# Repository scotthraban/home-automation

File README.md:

A collection of different parts of the home automation solution that I have built up over time for my house. The longer that things have been running, the less that I remember how they work, and where to find all the bits that go into each part of the whole.

So this is really more for me than for anyone else, but if anything I put up here ends up being helpful to anyone else, that would be awesome.

# Sensors
 - [ESP8266 Temperature Sensor](sensors/esp-temperature-sensor)
 - [Arduino Temperature Sensor (deprecated)](sensors/arduino-temperature-sensor)
 - [Arduino Temperature Humidity Sensor (deprecated)](sensors/arduino-temperature-humidity-sensor)
 - [ESP8266 AQI and Temperature Sensor](sensors/esp-air-quality-sensor)

# Controllers
 - [Arduino MySensors Furnance Controller (deprecated)](controllers/arduino-furnace-controller)

# Gateway
 - [Arduino MySensors Serial Gateway (deprecated)](openhab/arduino-serial-gateway)

# External Data Sources
 - [PurpleAir to openHAB over MQTT](purple-air)
 
# Notification / Alerting
 - [Telegram Bot](telegram-bot)

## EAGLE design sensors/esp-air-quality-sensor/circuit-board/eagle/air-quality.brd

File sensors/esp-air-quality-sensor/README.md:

# Air Quality Sensor

This project runs on an ESP8266, using MQTT over Wifi to send the air quality and temperature information back to openHAB.

## Software

[Arduino project for ESP8266 board](esp8266-mqtt-panasonic-air-quality-sensor).

## Wiring Schematic

## Circuit Board

[Eagle project](circuit-board/eagle)

I used the [OSH Park](https://oshpark.com/) service to fabricate the board for this project, sending them [just the board file](circuit-board/eagle/air-quality.brd).

## Project Box

Designed in Autodesk Fusion 360, available on [Thingiverse](https://www.thingiverse.com/thing:4777796).

## BOM

 - ESP-01S Wifi microcontroller ([something like this](https://www.amazon.com/gp/product/B01N98BTRH/ref=ppx_od_dt_b_asin_title_s00?ie=UTF8&psc=1))
 - [Panasonic SN-GCJA5](https://www.sparkfun.com/products/17123)
 - DS18B20 temperature sensor ([TO92](https://www.digikey.com/product-detail/en/maxim-integrated/DS18B20-/DS18B20--ND/956983)
 - AMS1117 3pin stepdown breakout board ([one of many to be found](https://www.amazon.com/gp/product/B07CP4P5XJ/ref=ppx_yo_dt_b_asin_title_o03_s00?ie=UTF8&psc=1))
 - 2x 4.7k Ohm resistors ([no particular reason to use these](https://www.amazon.com/gp/product/B0185FIIVE/ref=ppx_yo_dt_b_asin_title_o01_s00?ie=UTF8&psc=1))
 - 2.54mm Pitch 2X4 8 Pin Female Double Row Straight Header PCB Connector ([I used these](https://www.amazon.com/gp/product/B01IHBCO2K/ref=ppx_yo_dt_b_asin_title_o09_s00?ie=UTF8&psc=1))
 - USB Micro B power connector ([parallel](https://www.digikey.com/product-detail/en/amphenol-icc-fci/10118194-0001LF/609-4618-1-ND/2785382) or [perpendicular](https://www.digikey.com/product-detail/en/gct/USB3131-30-0230-A/2073-USB3131-30-0230-ACT-ND/9859713) to the board) 
 - 5v USB power supply (I just used one of the many that I have from dead cell phones and such)

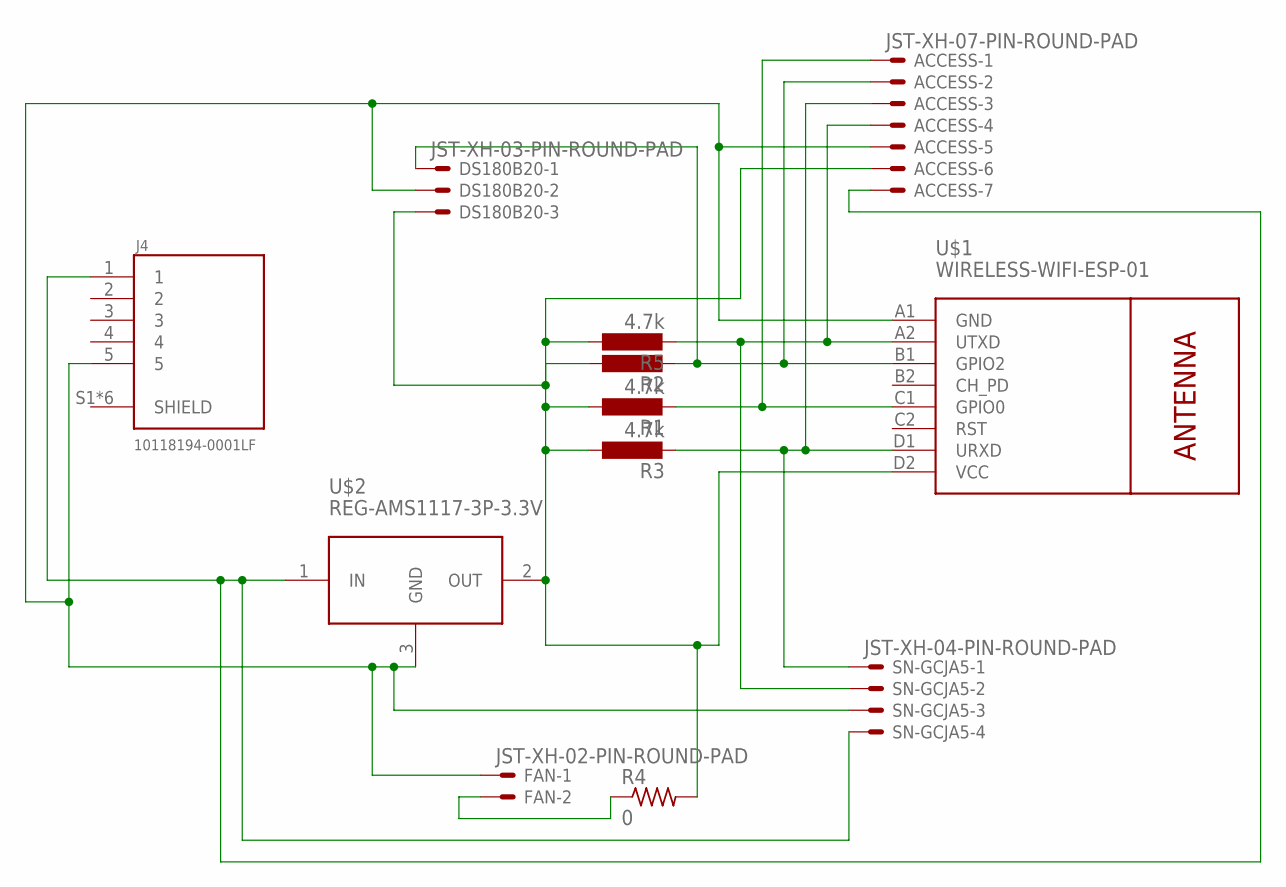
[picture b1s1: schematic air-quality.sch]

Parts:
ACCESS: JST-XH-07-PIN-ROUND-PAD; JST-XH-07-PACKAGE-ROUND-PAD
DS180B20: JST-XH-03-PIN-ROUND-PAD; JST-XH-03-PACKAGE-ROUND-PAD
FAN: JST-XH-02-PIN-ROUND-PAD; JST-XH-02-PACKAGE-ROUND-PAD
J4: 10118194-0001LF; AMPHENOL_10118194-0001LF
R1, R2, R3, R5: 4.7k; 0207/10
R4: 0; 0204V
SN-GCJA5: JST-XH-04-PIN-ROUND-PAD; JST-XH-04-PACKAGE-ROUND-PAD
U$1: WIRELESS-WIFI-ESP-01
U$2: REG-AMS1117-3P-3.3V; REG-AMS1117-3P

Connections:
3.3V: ACCESS.6, DS180B20.3, R1.1, R2.1, R3.1, R4.2, R5.1, U$1.D2 (VCC), U$2.2 (OUT)
5V: ACCESS.7, J4.1, SN-GCJA5.4, U$2.1 (IN)
GND: ACCESS.5, DS180B20.2, FAN.1, J4.5, SN-GCJA5.3, U$1.A1 (GND), U$2.3 (GND)
GPIO0: ACCESS.1, R1.2, U$1.C1 (GPIO0)
GPIO2: ACCESS.2, DS180B20.1, R2.2, U$1.B1 (GPIO2)
unnamed: FAN.2, R4.1
RX: ACCESS.3, R3.2, SN-GCJA5.1, U$1.D1 (URXD)
TX: ACCESS.4, R5.2, SN-GCJA5.2, U$1.A2 (UTXD)

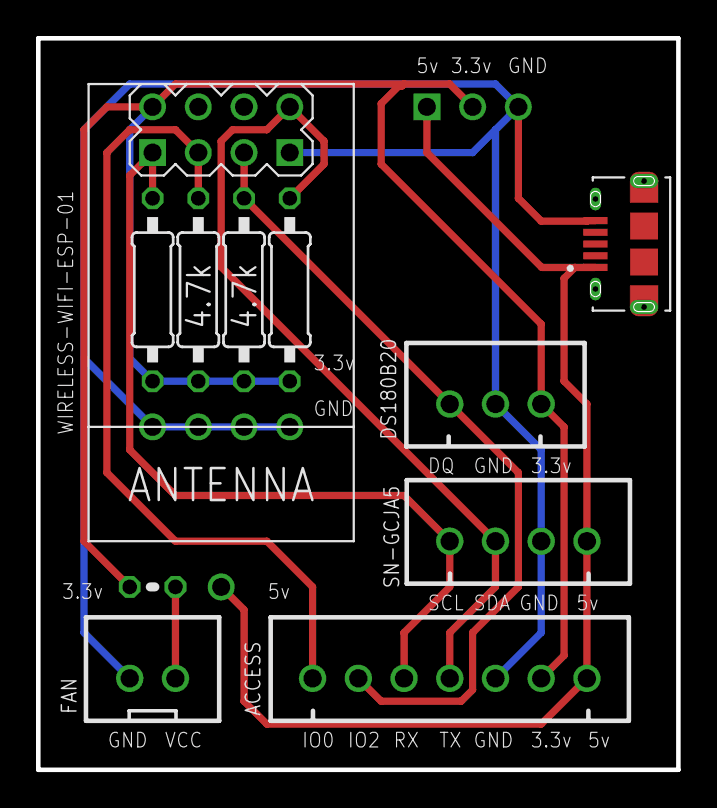
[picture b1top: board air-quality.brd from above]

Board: 2 copper layers, 35.6 x 40.6 mm, 12 parts (1 on the bottom side), 8 nets.

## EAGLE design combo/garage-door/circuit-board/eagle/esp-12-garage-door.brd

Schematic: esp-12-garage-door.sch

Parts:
2N2222: 2N2222-NPN-TO92-EBC; TO92-EBC
NODEMCU: NODEMCU
R2: 33; 0207/7
R3: 10k; 0207/7
R5: 470; 0207/7
R6: 1k; 0207/7
REED: REED_SWITCH-PTH-INSULATED; REED_SWITCH_PLASTIC
RELAY: JSM1-12V-5

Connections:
3V: NODEMCU.11 (3V), NODEMCU.25 (3V)
GND: 2N2222.E, NODEMCU.2 (GND), NODEMCU.10 (GND), NODEMCU.14 (GND), NODEMCU.17 (GND), NODEMCU.24 (GND), R3.2
unnamed: NODEMCU.15 (VIN), R2.2
unnamed: 2N2222.C, RELAY.5
unnamed: NODEMCU.28 (D2), R3.1, REED.P$2 (2)
unnamed: R2.1, RELAY.2
unnamed: 2N2222.B, R5.2
unnamed: NODEMCU.16 (3V), R6.1
unnamed: NODEMCU.29 (D1), R5.1
unnamed: R6.2, REED.P$1 (1)

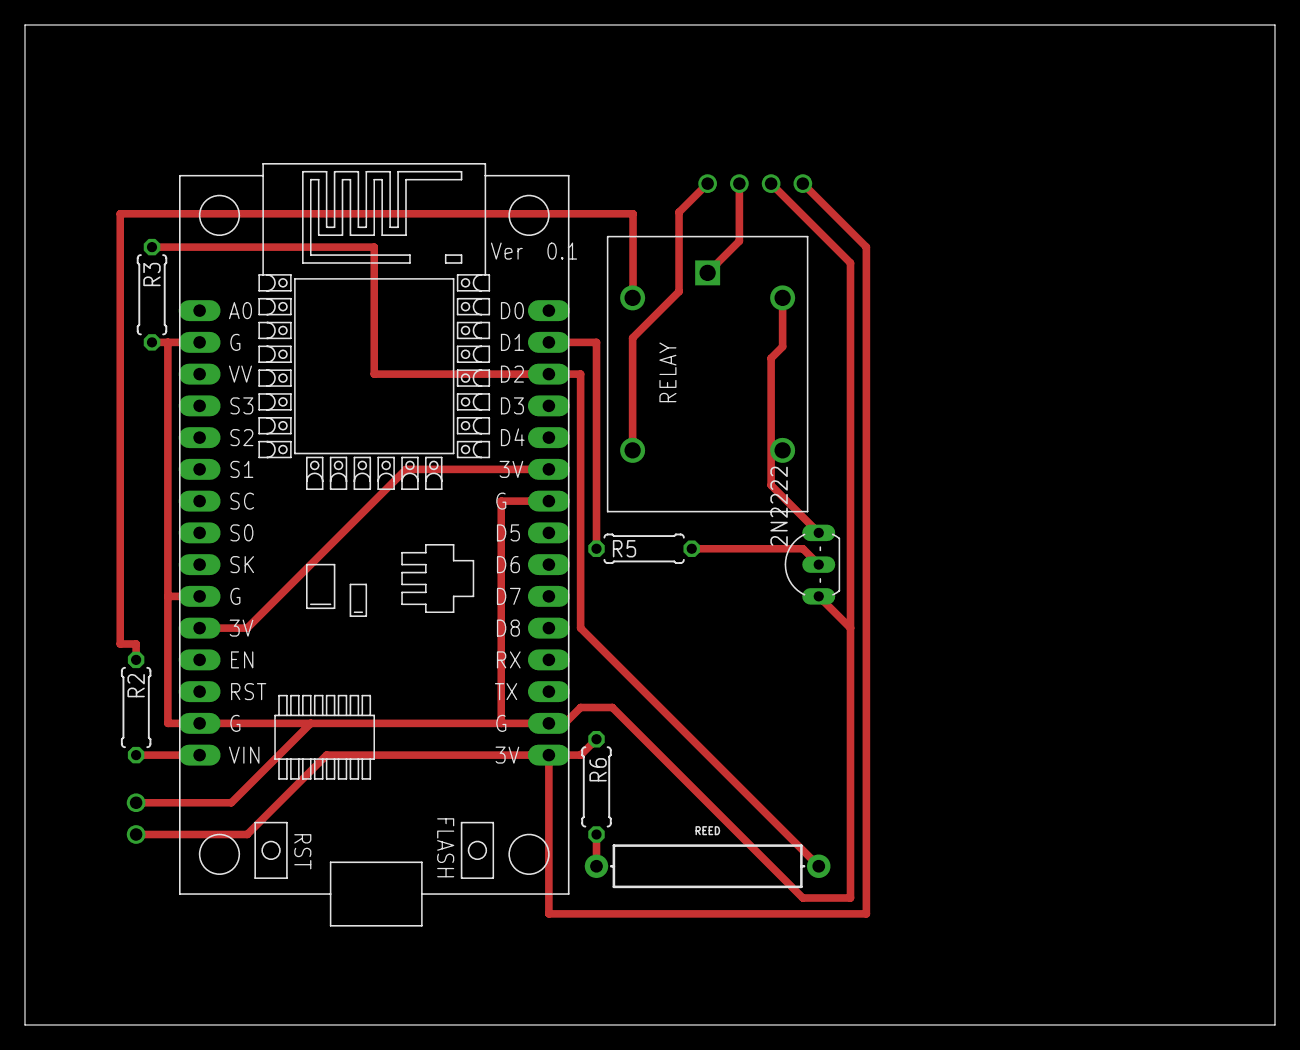
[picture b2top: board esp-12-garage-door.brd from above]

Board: 2 copper layers, 100.0 x 80.0 mm, 8 parts (0 on the bottom side), 10 nets.

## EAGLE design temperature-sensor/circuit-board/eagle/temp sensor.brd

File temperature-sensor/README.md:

# Temperature Sensor

This project runs on an ESP8266, using MQTT over Wifi to send the temperature back to openHAB.

I created a custom circuit board to make it a little more durable and reliable.

I have used both the TO92 and the waterproof probes.

I ran into a fair bit of issues with heat from the components being picked up by the sensor, even with the extended traces on the circuit board. In the end I gave on on elegant solutions and just stuck a fan on the thing to keep the ambient air circulating over the sensor. The fan is only being driven by 5v, but I used a 12v fan so that it would spin slow, and thus be quiet, to assist in the WAF of the project. Unfortunately that also meant that the fan sometimes does not have enough voltage to start spinning - once it is going it is fine, but it sometimes needs a push.

## Software

[Arduino project for ESP8266 board](esp8266-mqtt-single-ds18b20-sensor).

## Wiring Schematic

## Circuit Board

[Eagle project](circuit-board)

I used the [OSH Park](https://oshpark.com/) service to fabricate the board for this project, sending them [this zip file](circuit-board/export/temp sensor_2020-01-11.zip) with the Gerber (and other) files.

## Project Box

Designed in Autodesk Fusion 360, available on [Thingiverse](https://www.thingiverse.com/thing:4508169).

## BOM

 - ESP-01S Wifi microcontroller ([something like this](https://www.amazon.com/gp/product/B01N98BTRH/ref=ppx_od_dt_b_asin_title_s00?ie=UTF8&psc=1))
 - DS18B20 temperature sensor ([TO92](https://www.digikey.com/product-detail/en/maxim-integrated/DS18B20-/DS18B20--ND/956983) or [waterproof](https://www.amazon.com/Gikfun-DS18B20-Temperature-Waterproof-EK1083x3/dp/B012C597T0/ref=sr_1_3?crid=3AA1NY9ENGP12&dchild=1&keywords=ds18b20&qid=1593380354&sprefix=ds18%2Caps%2C232&sr=8-3))
 - AMS1117 3pin stepdown breakout board ([one of many to be found](https://www.amazon.com/gp/product/B07CP4P5XJ/ref=ppx_yo_dt_b_asin_title_o03_s00?ie=UTF8&psc=1))
 - 2x 4.7k Ohm resistors ([no particular reason to use these](https://www.amazon.com/gp/product/B0185FIIVE/ref=ppx_yo_dt_b_asin_title_o01_s00?ie=UTF8&psc=1))
 - 2.54mm Pitch 2X4 8 Pin Female Double Row Straight Header PCB Connector ([I used these](https://www.amazon.com/gp/product/B01IHBCO2K/ref=ppx_yo_dt_b_asin_title_o09_s00?ie=UTF8&psc=1))
 - 30x30x10mm 2pin 12v computer fan ([not great but it worked](https://www.amazon.com/gp/product/B071KK1KBG/ref=ppx_yo_dt_b_asin_title_o09_s00?ie=UTF8&psc=1))
 - USB Micro B power connector ([parallel](https://www.digikey.com/product-detail/en/amphenol-icc-fci/10118194-0001LF/609-4618-1-ND/2785382) or [perpendicular](https://www.digikey.com/product-detail/en/gct/USB3131-30-0230-A/2073-USB3131-30-0230-ACT-ND/9859713) to the board) 
 - 5v USB power supply (I just used one of the many that I have from dead cell phones and such)

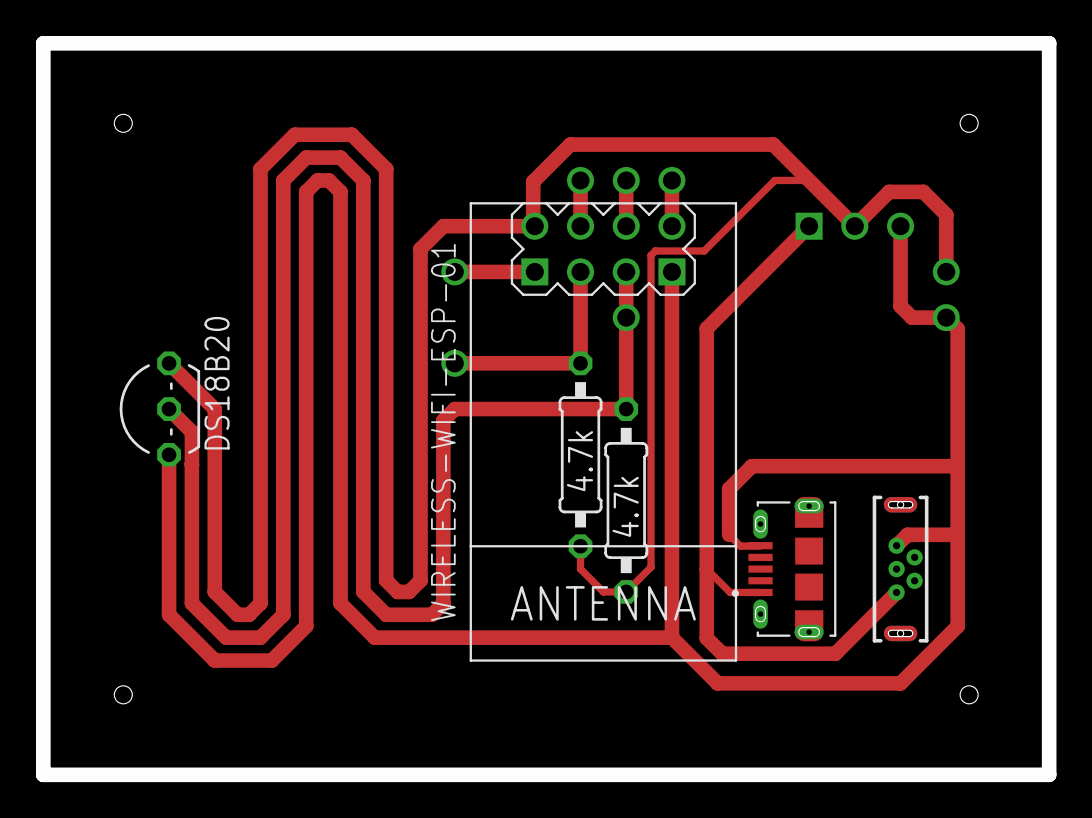
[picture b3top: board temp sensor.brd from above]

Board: 2 copper layers, 55.9 x 40.6 mm, 7 parts (1 on the bottom side), 5 nets.

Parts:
IC1: DS18B20; TO92-
J1: USB3131-XX-0230-X_REVB; GCT_USB3131-XX-0230-X_REVB
J4: 10118194-0001LF; AMPHENOL_10118194-0001LF
R1, R2: 4.7k; 0207/10
U$1: WIRELESS-WIFI-ESP-01
U$2: REG-AMS1117-3P-3.3V; REG-AMS1117-3P

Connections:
3.3V: IC1.3, R1.1, R2.1, U$1.D2, U$2.2
5V: J1.1, J4.1, U$2.1
GND: IC1.1, J1.5, J4.5, U$1.A1, U$2.3
GPIO0: R1.2, U$1.C1
GPIO2: IC1.2, R2.2, U$1.B1

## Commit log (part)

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2020-06-28 initial setup of gh pages
2020-06-28 Rename README.md to index.md
2020-06-28 Set theme jekyll-theme-slate
2020-06-28 removed frontmatter test page
2020-06-28 adding gitignore, ignoring jekyll output
2020-06-29 adding temperature sensor project
2020-06-29 adding gemfile for local gh pages testing
2020-06-29 remove temp "other" directory
2020-06-29 adding a skeleton for the front page
2020-06-29 fix typo in link to temperature sensor page
2020-07-04 add openhab favicon
2020-07-04 move favicon to the root
2020-07-05 moved temp sensor to nested dir
2020-07-05 adding older my sensors arduino code
2020-07-05 readme for arduino furnace controller
2020-07-05 arduino serial gateway
2020-07-05 arduino temp and temp/humidity sensors
2020-07-05 fix ; --> : typo
2020-07-05 fix Furnance -- Furnace typo
2020-07-26 garage door controller/sensor esp-12e project
2020-07-26 garage door eagle files
2020-09-17 raspberry pi tts server
2020-10-12 initial commit for offline aqi for Geri
2020-10-14 3 lines output, no button
2020-10-14 button interrupt added
2020-10-17 ESP-01 AQI / Temp Sensor project
2020-10-17 Add AQI/Temp sensor
2021-02-27 convert combo to use home assistant config / keep alive topics
2021-02-27 add aqi/temp project box image and link to thingiverse
2021-03-01 temp only sensor add config/avail topics
2021-03-01 garage door config/avail/state/command topics
2021-09-06 libraries, secure mqtt
2021-09-06 add purpleair script
2021-09-06 added the telegram bot
2021-09-06 fix link to purple air section
2021-10-23 add missed openhab getCommandTopic definition to .h
2021-10-23 actually assign messageCallback to object, not to itself
2021-10-23 refactor garage door switch to use openhab lib
2021-10-23 refactor garage freezer to use common libraries
2022-06-08 update tts service to python 3 and add .service file
2022-06-08 add readme for tts service
2022-06-11 switch to new purple air api
2022-07-19 purple-air - lock in python library versions
2022-07-19 purple-air - use fields to index into data
2022-12-26 Bump wheel from 0.37.1 to 0.38.1 in /purple-air
    Bumps [wheel](https://github.com/pypa/wheel) from 0.37.1 to 0.38.1.
    - [Release notes](https://github.com/pypa/wheel/releases)
    - [Changelog](https://github.com/pypa/wheel/blob/main/docs/news.rst)
    - [Commits](https://github.com/pypa/wheel/compare/0.37.1...0.38.1)
    ---
    updated-dependencies:
2022-12-31 bump python to 3.11
2022-12-31 bump wheel to 0.38.4, fix regex security issue
2022-12-31 add retry after timeout, let exception get to top level to fail script
2023-01-18 change purple-air build version to 0.9
2023-05-22 Create arm64 docker build.sh for grafana-image-renderer
2023-05-22 Create README.md for grafana-image-renderer
2024-07-03 add better context in HA registration config
2024-07-03 bump requests for security issues
2025-08-19 fix build script to work with podman
2025-09-01 Create WifiConfig.h template
2025-09-01 Create MqttConfig.h template
2025-09-01 Create SensorConfig.h template
2026-01-25 Bump requests from 2.32.0 to 2.32.4 in /purple-air
    Bumps [requests](https://github.com/psf/requests) from 2.32.0 to 2.32.4.
    - [Release notes](https://github.com/psf/requests/releases)
    - [Changelog](https://github.com/psf/requests/blob/main/HISTORY.md)
    - [Commits](https://github.com/psf/requests/compare/v2.32.0...v2.32.4)
    ---
    updated-dependencies:
2026-03-26 Bump requests from 2.32.4 to 2.33.0 in /purple-air
    Bumps [requests](https://github.com/psf/requests) from 2.32.4 to 2.33.0.
    - [Release notes](https://github.com/psf/requests/releases)
    - [Changelog](https://github.com/psf/requests/blob/main/HISTORY.md)
    - [Commits](https://github.com/psf/requests/compare/v2.32.4...v2.33.0)
    ---
    updated-dependencies:
2026-06-13 Add /ping health endpoint

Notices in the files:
parts and their libraries:
SparkFun-Switches: Licensing: Creative Commons ShareAlike 4.0 International - https://creativecommons.org/licenses/by-sa/4.0
diy-modules: Released under the Creative Commons Attribution 4.0 International License: http://creativecommons.org/licenses/by/4.0
